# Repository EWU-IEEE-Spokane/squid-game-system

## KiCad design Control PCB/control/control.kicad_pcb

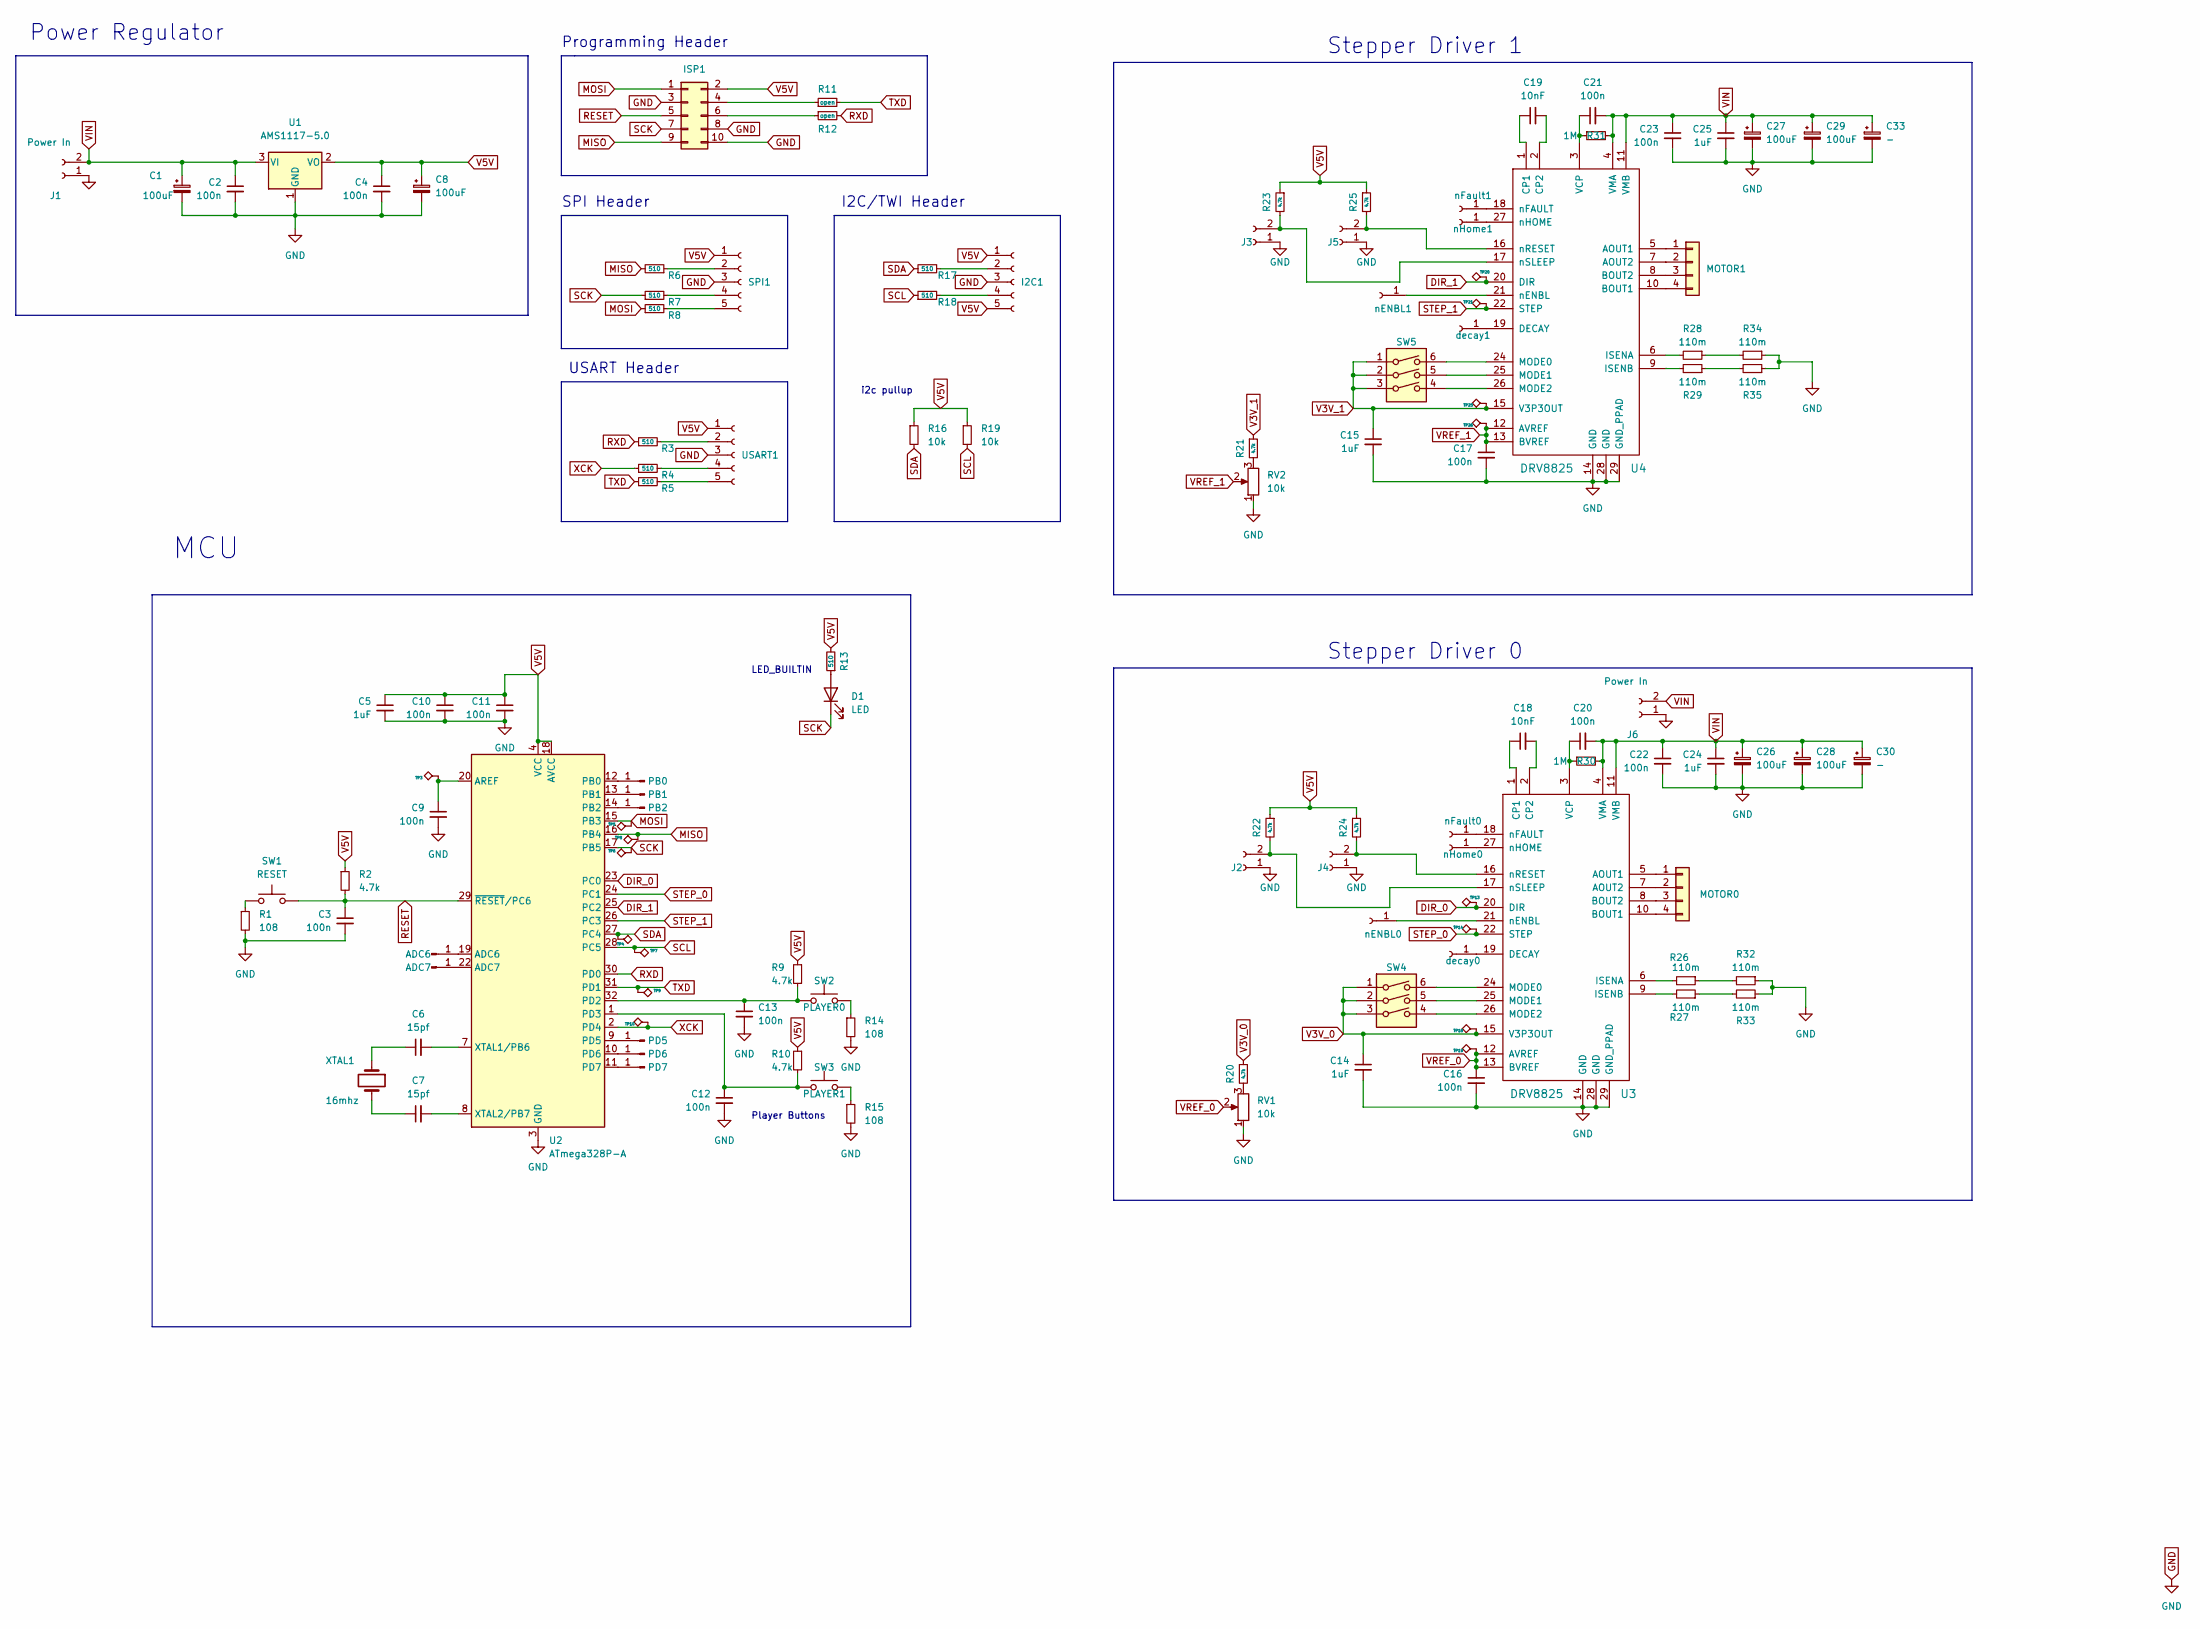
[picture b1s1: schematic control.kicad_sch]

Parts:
ADC6, ADC7: -; PinHeader_1x01_P2.54mm_Vertical
C1, C8, C26, C27, C28, C29: 100uF; CP_Radial_D10.0mm_P5.00mm
C2, C3, C4, C9, C10, C11, C12, C13, C16, C17, C20, C21, C22, C23: 100n; C_0805_2012Metric
C5, C14, C15, C24, C25: 1uF; C_0805_2012Metric
C6, C7: 15pf; C_0805_2012Metric
C18, C19: 10nF; R_0805_2012Metric_Pad1.20x1.40mm_HandSolder
C30, C33: -; CP_Radial_D10.0mm_P5.00mm
D1: LED; LED_D5.0mm
I2C1: -; PinHeader_1x05_P2.54mm_Vertical
ISP1: ISP; PinHeader_2x05_P2.54mm_Vertical
J1, J6: Power In; PinHeader_1x02_P2.54mm_Vertical
J2, J3, J4, J5: RST; PinHeader_1x02_P2.54mm_Vertical
MOTOR0, MOTOR1: -; PinHeader_1x04_P2.54mm_Vertical
PB0, PB1, PB2: -; PinHeader_1x01_P2.54mm_Vertical
PD5, PD6, PD7: -; PinHeader_1x01_P2.54mm_Vertical
R1, R14, R15: 108; R_0805_2012Metric_Pad1.20x1.40mm_HandSolder
R2, R9, R10, R20, R21, R22, R23, R24, R25: 4.7k; R_0805_2012Metric_Pad1.20x1.40mm_HandSolder
R3, R4, R5, R6, R7, R8, R13, R17, R18: 510; R_0805_2012Metric_Pad1.20x1.40mm_HandSolder
R11, R12: open; R_0805_2012Metric_Pad1.20x1.40mm_HandSolder
R16, R19: 10k; R_0805_2012Metric_Pad1.20x1.40mm_HandSolder
R26, R27, R28, R29, R32, R33, R34, R35: 110m; R_0612_1632Metric_Pad1.18x3.40mm_HandSolder
R30, R31: 1M; R_0805_2012Metric_Pad1.20x1.40mm_HandSolder
RV1, RV2: 10k; PinHeader_1x03_P2.54mm_Vertical
SPI1: -; PinHeader_1x05_P2.54mm_Vertical
SW1: RESET; SW_Push_1P1T_NO_CK_KSC6xxJ
SW2: PLAYER0; PinHeader_1x02_P2.54mm_Vertical
SW3: PLAYER1; PinHeader_1x02_P2.54mm_Vertical
SW4, SW5: MODE; SW_DIP_SPSTx03_Slide_6.7x9.18mm_W7.62mm_P2.54mm_LowProfile
TP3, TP4, TP5, TP6, TP7, TP8, TP9, TP10, TP13, TP14, TP18, TP19, TP20, TP21, TP25, TP26: -; testpoint
U1: AMS1117-5.0; SOT-223-3_TabPin2
U2: ATmega328P-A; TQFP-32_7x7mm_P0.8mm
U3, U4: DRV8825; HTSSOP-28_4.4x9.7mm_Pitch0.65mm_ThermalPad
USART1: -; PinHeader_1x05_P2.54mm_Vertical
XTAL1: 16mhz; Resonator-2Pin_W10.0mm_H5.0mm
decay0, decay1: -; PinHeader_1x01_P2.54mm_Vertical
nENBL0, nENBL1: -; PinHeader_1x01_P2.54mm_Vertical
nFault0, nFault1: -; PinHeader_1x01_P2.54mm_Vertical
nHome0, nHome1: -; PinHeader_1x01_P2.54mm_Vertical

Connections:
DIR_0: TP13.1, U2.23 (PC0), U3.20 (DIR)
DIR_1: TP20.1, U2.25 (PC2), U4.20 (DIR)
GND: C1.2, C2.2, C3.2, C4.2, C5.2, C8.2, C9.2, C10.2, C11.2, C12.2, C13.2, C14.2, C15.2, C16.2, C17.2, C22.2, C23.2, C24.2, C25.2, C26.2, C27.2, C28.2, C29.2, C30.2, C33.2, I2C1.3, ISP1.3, ISP1.8, ISP1.10, J1.1, J2.1, J3.1, J4.1, J5.1, J6.1, R1.2, R14.2, R15.2, R32.1, R33.1, R34.1, R35.1, RV1.1, RV2.1, SPI1.3, U1.1 (GND), U2.3 (GND), U2.5 (GND), U2.21 (GND), U3.14 (GND), U3.28 (GND), U3.29 (GND_PPAD), U4.14 (GND), U4.28 (GND), U4.29 (GND_PPAD), USART1.3
MISO: ISP1.9, R6.2, TP8.1, U2.16 (PB4)
MOSI: ISP1.1, R8.1, TP5.1, U2.15 (PB3)
unnamed: ADC6.1, U2.19 (ADC6)
unnamed: ADC7.1, U2.22 (ADC7)
unnamed: C6.1, XTAL1.1
unnamed: C6.2, U2.7 (XTAL1/PB6)
unnamed: C7.1, XTAL1.2
unnamed: C7.2, U2.8 (XTAL2/PB7)
unnamed: C9.1, TP3.1, U2.20 (AREF)
unnamed: C12.1, R10.2, SW3.1, U2.1 (PD3)
unnamed: C13.1, R9.2, SW2.1, U2.32 (PD2)
unnamed: C18.1, U3.1 (CP1)
unnamed: C18.2, U3.2 (CP2)
unnamed: C19.1, U4.1 (CP1)
unnamed: C19.2, U4.2 (CP2)
unnamed: C20.1, R30.1, U3.3 (VCP)
unnamed: C21.1, R31.1, U4.3 (VCP)
unnamed: D1.2 (A), R13.1
unnamed: I2C1.2, R17.2
unnamed: I2C1.4, R18.2
unnamed: ISP1.4, R11.1
unnamed: ISP1.6, R12.1
unnamed: J2.2, R22.2, U3.17 (nSLEEP)
unnamed: J3.2, R23.2, U4.17 (nSLEEP)
unnamed: J4.2, R24.2, U3.16 (nRESET)
unnamed: J5.2, R25.2, U4.16 (nRESET)
unnamed: MOTOR0.1, U3.5 (AOUT1)
unnamed: MOTOR0.2, U3.7 (AOUT2)
unnamed: MOTOR0.3, U3.8 (BOUT2)
unnamed: MOTOR0.4, U3.10 (BOUT1)
unnamed: MOTOR1.1, U4.5 (AOUT1)
unnamed: MOTOR1.2, U4.7 (AOUT2)
unnamed: MOTOR1.3, U4.8 (BOUT2)
unnamed: MOTOR1.4, U4.10 (BOUT1)
unnamed: PB0.1, U2.12 (PB0)
unnamed: PB1.1, U2.13 (PB1)
unnamed: PB2.1, U2.14 (PB2)
unnamed: PD5.1, U2.9 (PD5)
unnamed: PD6.1, U2.10 (PD6)
unnamed: PD7.1, U2.11 (PD7)
unnamed: R1.1, SW1.1
unnamed: R3.2, USART1.2
unnamed: R4.2, USART1.4
unnamed: R5.2, USART1.5
unnamed: R6.1, SPI1.2
unnamed: R7.2, SPI1.4
unnamed: R8.2, SPI1.5
unnamed: R14.1, SW2.2
unnamed: R15.1, SW3.2
unnamed: R20.2, RV1.3
unnamed: R21.2, RV2.3
unnamed: R26.1, R32.2
unnamed: R27.1, R33.2
unnamed: R28.1, R34.2
unnamed: R28.2, U4.6 (ISENA)
unnamed: R29.1, R35.2
unnamed: R29.2, U4.9 (ISENB)
unnamed: SW4.4, U3.26 (MODE2)
unnamed: SW4.5, U3.25 (MODE1)
unnamed: SW4.6, U3.24 (MODE0)
unnamed: SW5.4, U4.26 (MODE2)
unnamed: SW5.5, U4.25 (MODE1)
unnamed: SW5.6, U4.24 (MODE0)
unnamed: R26.2, U3.6 (ISENA)
unnamed: R27.2, U3.9 (ISENB)
unnamed: U3.18 (nFAULT), nFault0.1
unnamed: U3.19 (DECAY), decay0.1
unnamed: U3.21 (nENBL), nENBL0.1
unnamed: U3.27 (nHOME), nHome0.1
unnamed: U4.18 (nFAULT), nFault1.1
unnamed: U4.19 (DECAY), decay1.1
unnamed: U4.21 (nENBL), nENBL1.1
unnamed: U4.27 (nHOME), nHome1.1
RESET: C3.1, ISP1.5, R2.2, SW1.2, U2.29 (~RESET/PC6)
RXD: R3.1, R12.2, U2.30 (PD0)
SCK: D1.1 (K), ISP1.7, R7.1, TP6.1, U2.17 (PB5)
SCL: R18.1, R19.2, TP7.1, U2.28 (PC5)
SDA: R16.2, R17.1, TP4.1, U2.27 (PC4)
STEP_0: TP14.1, U2.24 (PC1), U3.22 (STEP)
STEP_1: TP21.1, U2.26 (PC3), U4.22 (STEP)
TXD: R5.1, R11.2, TP9.1, U2.31 (PD1)
V3V_0: C14.1, R20.1, SW4.1, SW4.2, SW4.3, TP18.1, U3.15 (V3P3OUT)
V3V_1: C15.1, R21.1, SW5.1, SW5.2, SW5.3, TP25.1, U4.15 (V3P3OUT)
V5V: C4.1, C5.1, C8.1, C10.1, C11.1, I2C1.1, I2C1.5, ISP1.2, R2.1, R9.1, R10.1, R13.2, R16.1, R19.1, R22.1, R23.1, R24.1, R25.1, SPI1.1, U1.2 (VO), U2.4 (VCC), U2.6 (VCC), U2.18 (AVCC), USART1.1
VIN: C1.1, C2.1, C20.2, C21.2, C22.1, C23.1, C24.1, C25.1, C26.1, C27.1, C28.1, C29.1, C30.1, C33.1, J1.2, J6.2, R30.2, R31.2, U1.3 (VI), U3.4 (VMA), U3.11 (VMB), U4.4 (VMA), U4.11 (VMB)
VREF_0: C16.1, RV1.2, TP19.1, U3.12 (AVREF), U3.13 (BVREF)
VREF_1: C17.1, RV2.2, TP26.1, U4.12 (AVREF), U4.13 (BVREF)
XCK: R4.1, TP10.1, U2.2 (PD4)

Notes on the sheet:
Player Buttons
Stepper Driver 0
USART Header
SPI Header
i2c pullup
I2C/TWI Header
MCU
Stepper Driver 1
LED_BUILTIN
Power Regulator
Programming Header

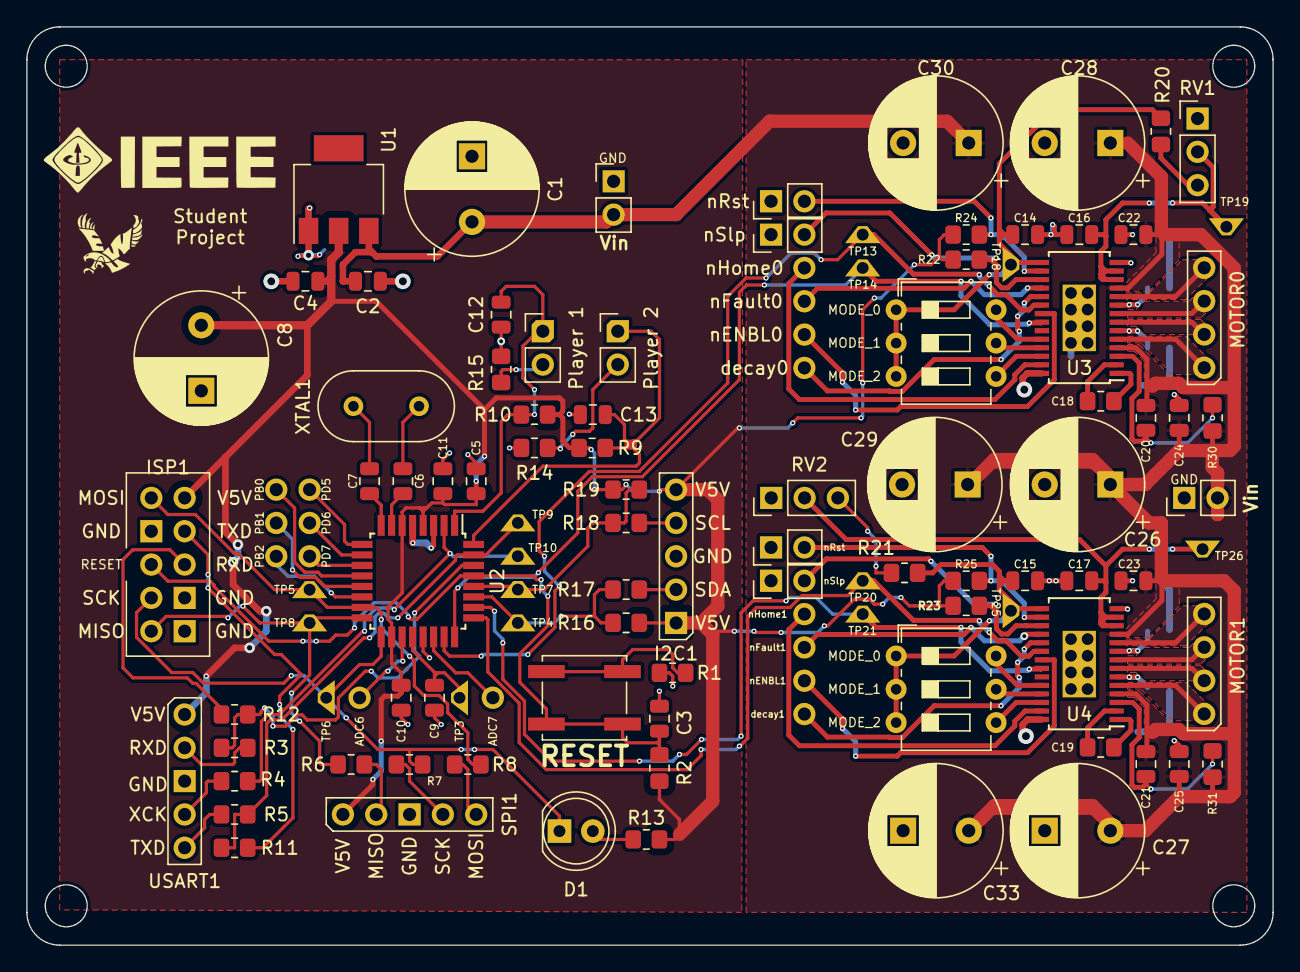
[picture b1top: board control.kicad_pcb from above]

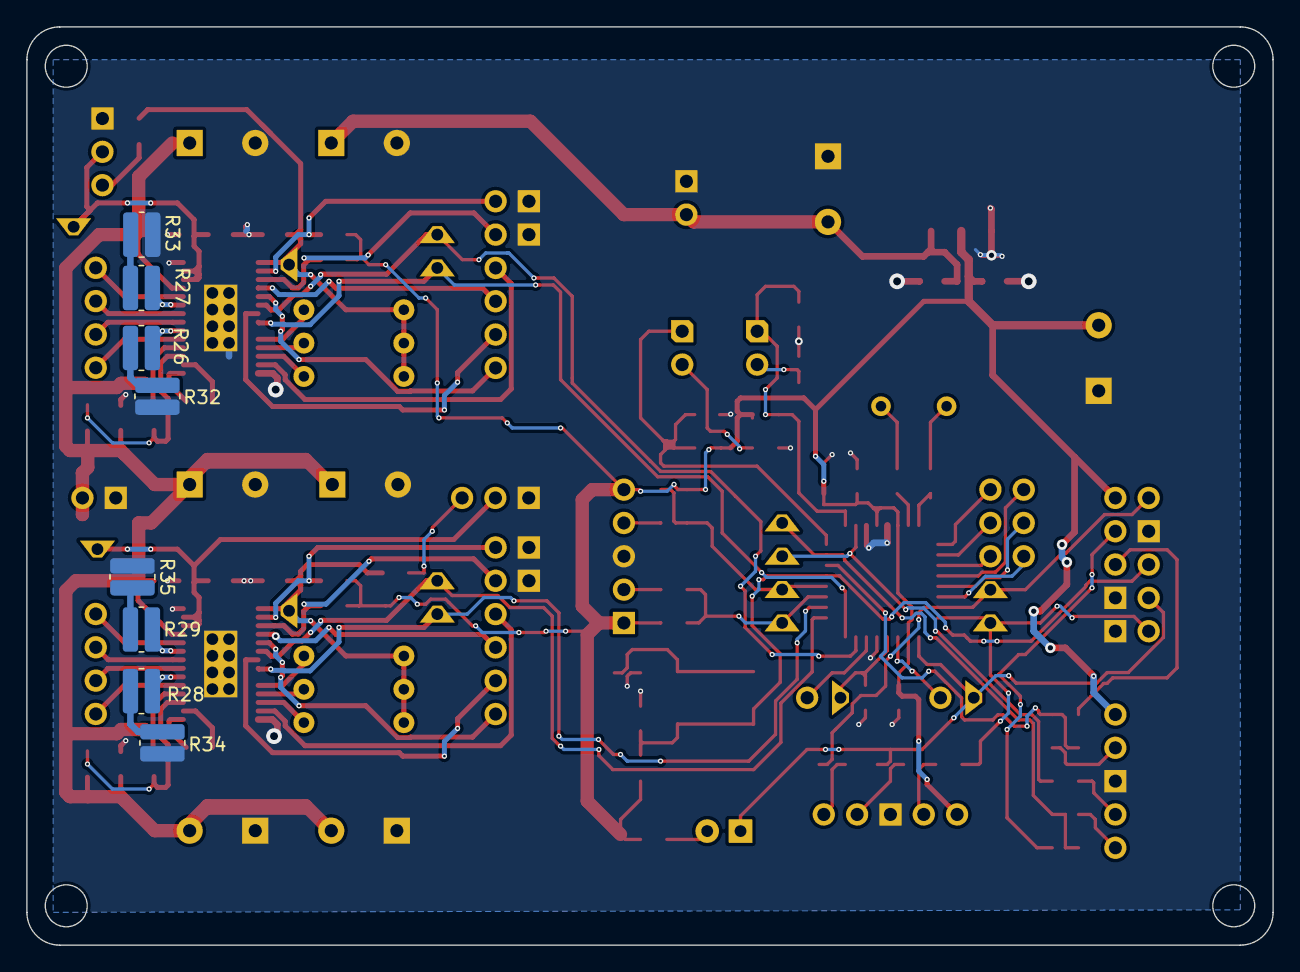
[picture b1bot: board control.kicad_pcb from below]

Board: 2 copper layers, 95.0 x 70.0 mm, 123 parts (8 on the bottom side), 91 nets.

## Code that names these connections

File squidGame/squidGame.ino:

#include "stepperControl.h"
#include <stdint.h>

#define RED_LED 3 // check for the correct pin

stepper stepper0(15, 14); // PC1, PC0
stepper stepper1(17, 16);  // PC3, PC2
stepper headStepper(6, 7); // PD6, PD7

const uint16_t player_step = 10;

// timing variables 
unsigned long start_millis;
unsigned long current_millis;
unsigned long period;

const uint16_t red_time_max = 5000; // milliseconds
const uint16_t red_time_min = 1000; // milliseconds
const uint16_t red_flash_time = 125; // milliseconds
const uint16_t green_time_max = 7000; // miliseconds
const uint16_t green_time_min = 3000; // milliseconds



class counter_ {
	public:
	const int8_t enable_pin = 8;	//PB0
	const int8_t status_pin = 9;	//PB1
	const int8_t reset_pin	= 10;	//PB2
	
	bool getStatus(void) {
		return digitalRead(status_pin);
	}
	
	void reset(void) {
		digitalWrite(enable_pin, LOW);
		digitalWrite(reset_pin, HIGH);
		delay(10);
		digitalWrite(reset_pin, LOW);
	}
	
	void start(void) {
		digitalWrite(enable_pin, HIGH);
	}
	
	counter_() {
		pinMode(enable_pin, OUTPUT);
		pinMode(status_pin, INPUT);
		pinMode(reset_pin, OUTPUT);
		
		digitalWrite(reset_pin, LOW);
		digitalWrite(enable_pin, LOW);
	}
} counter;

class player_ {
	public:
	uint8_t pin;
	bool lastState;
	bool playing;
	bool hasChanged(void){
		if (digitalRead(pin) != lastState) {
			lastState != lastState;
			return true;
		}
		return false;
	}
	
	bool state(void){
		return digitalRead(pin);
	}
	player_(uint8_t digitalPin){
		lastState =0;
		pin=digitalPin;
	}
};
player_ player0(2); //PD2
player_ player1(3); //PD3

void setup(){
	Timer2.begin();
	Serial.begin(115200);
	stepper0.speedDivisor = 3;
	stepper1.speedDivisor = 3;
	headStepper.speedDivisor = 3;
	
	digitalWrite(RED_LED, HIGH);
}

void loop(){ 
	player0.playing = true; 
	player1.playing = true;
	
	counter.reset();
	delay(3000);
	
	//wait for start
	while(!player1.state() || !player0.state()){};
	
	//startup
	Serial.write("play rules.wav");
	Serial.flush();
	delay(15000);
	
	while (player0.playing || player1.playing){
		{ //GREEN LIGHT
			Serial.write("play green_light.wav\n");  // play green light sound
			Serial.flush();
			headStepper.incrementalMove(100);  // rotate head 180 degrees
			headStepper.waitUntilStopped();
			unsigned long endTime = millis() + random(green_time_min, green_time_max);
			while (millis() < endTime){

				// checking if the players ran out of time
				if (counter.getStatus()){
					player0.playing = false;
					player1.playing = false;
				}
				// read button state and move players
				if(player0.hasChanged() && player0.playing){
					stepper0.incrementalMove(player_step);  // move player forward need to dial in the right value 
					stepper0.waitUntilStopped();
				}
				if(player1.hasChanged() && player1.playing){
					stepper1.incrementalMove(player_step);  // move player forward need to dial in the right value 
					stepper1.waitUntilStopped();
				}
			}
		}
		
		{ // RED LIGHT
			Serial.write("play red_light_quick.wav\n");  // play red light sound
			Serial.flush();
			
			headStepper.incrementalMove(-100);  // rotate head -180 degrees
			for(int i = 0; i < 10; i++){
				delay(50);
				digitalWrite(RED_LED, !digitalRead(RED_LED));
			}
			headStepper.waitUntilStopped();
			
			// RED LIGHT SOLID
			unsigned long endTime = millis() + random(green_time_min, green_time_max);
			while (millis() < endTime){
				if (counter.getStatus()){
					player0.playing = false;
					player1.playing = false;
				}
				// read button state and check players
				if(player0.state() && player0.playing){
					player0.playing = false;
				}
				if(player1.state() && player1.playing){
					player1.playing = false;
				}
			}
		}
	}
}

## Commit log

2022-09-03 Initial PCB design
2022-09-05 PCB Fabrication Outputs
2022-09-07 Wrote stepper motor control interface.
2022-09-07 Added stepper::getCurrentPosition() method. Small tweeks.
    Small formatting changes.
    Added volatile to speedDivisor, as it's shared.
    Changed a few comments to be clearer.
2022-09-07 Added folder & stub file for sound player
2022-09-08 Numerous improvements. Changed stepper::tick() frequency from 2khz to 4khz
    1. Changed _Timer to Timer_
    (Names beginning with _ are reserved by the language)
    2. Changed MAX_SUBSCRIBERS_TIMER2 to const uint8_t maxSubscribers, moved it into the Timer_ class.
    (It's existence as a macro implied, incorrectly, that it could be changed there. Changes to the max subscriber count would also require changes to the timer hardware setup in Timer_::begin() )
    3. Made handling of Timer_::subscriber type safe
    4. Added stepper_error(char *errMsg) for unrecoverable errors. Prints errMsg in a loop to the serial output. Changed Timer_::subscribe to use this function.
2022-09-08 Changed github tab spacing to 4
2022-09-08 Made all stepper member functions safe to access anywhere
2022-09-08 Removed debugging code that was mistakingly included.
2022-09-08 stepper::stepHigh doesn't need to be volatile.
2022-09-10 Modified stepper::tick() to respect DRV8825 timing requirements.
    There must be a minimum wait time between changing "DIR" and issuing a pulse at "STEP" of 650ns. Before this change, there was a delay of only 680ns.
    I placed the other useful work in the same code block inbetween the two writes, and added an assembly line to force the compiler to respect ordering. The delay is now ~1600ns which leaves some breath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
    This change made stepper::tick() ~4 clock cycles longer in the worse case. (Redundant reads caused by the barriers)
2022-09-10 Testing various functions. Code example
2022-09-11 Fix compiler warnings
2022-09-12 Fix support for multiple stepper motors.
    missing tickCount++; in Timer_::tick()
    Update Timer2_::begin() accordingly, to fix tick rate.
2022-09-17 Started game logic
    Jeremy & Justin
2022-10-08 Remove old testing code
2022-10-08 Place things in folder, as needed by arduino ide
2022-10-08 Fix whitespace
2022-10-08 Fix type error
2022-10-08 fix errors
2022-10-08 Code Refactoring
2023-09-26 Faster operation of the timer - 4 times as fast
    Allows finer-grained control of stepper motor speed.
2023-09-26 Faster stepper operation - 8x
    Allows finer grained control of stepper motor speed.
2023-09-26 Change timer maximum subscribers number to 2 for faster stepper ticks
